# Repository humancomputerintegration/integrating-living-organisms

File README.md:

# Integrating Living Organisms to Implement Care-based Interactions

This repository contains design files to replicate the slime mold integrated smartwatch presented in the paper ["Integrating Living Organisms to Implement Care-based Interactions"](https://dl.acm.org/doi/abs/10.1145/3526113.3545629), which appeared at UIST2022. The smartwatch is a prototype exploring a living media interface that requires the user to care for the organism (slime mold, aka Physarum Polycephalum) that is integrated inside it in order for the functionality (it's heart rate sensor) to work. This device was designed by Jasmine Lu and Pedro Lopes at the University of Chicago's [Human Computer Integration Lab](https://lab.plopes.org).

[Paper](https://lab.plopes.org/published/2022-UIST-IntegratingLivingOrganisms.pdf) | [Video](https://youtu.be/Bex91KV56PQ) | [UIST'22 Talk](https://youtu.be/VkC54ZNO_HU?t=18566)

## Device Hardware
The slime mold integrated smart watch is a standard maker-friendly smartwatch with a display, RTC, and heart rate sensor. However, it's specifically engineered to rely on the slime mold to form a conductive wire. An overview of the whole system can be seen below.

### Device Components
Below is a list of all the components required for to make this device. For the enclosures, the current design does require access to a 3D printer and a laser cutter. The current design also requires the manufacturing of a PCB (and ordering of small electronic components). 

#### Materials
* Clear acrylic sheets (2mm and 1.5mm)
* Acrylic Glue
* PLA for 3D printing
* Watch Strap - [Amazon Link](https://www.amazon.com/gp/product/B085PXB8CV/)
* Neodynium Magnets (6mm x 2mm and 3mm x 2mm) - [Link 1](https://www.amazon.com/gp/product/B07KJ9H31P) [Link 2](https://www.amazon.com/ETHCOOL-Magnets-Warhammer-Miniatures-Projects/dp/B09MVYGX1X)
* Copper Tape

#### Electronic Components
* Seeeduino Xiao Microcontroller - [Link](https://www.seeedstudio.com/Seeeduino-XIAO-Arduino-Microcontroller-SAMD21-Cortex-M0+-p-4426.html)
* MAX3010X Heart Rate Sensor Breakout - [Link](https://www.amazon.com/dp/B08ZNFF7H2)
* Lithium Battery Charging Module - [Link](https://www.amazon.com/Lithium-Battery-Charging-Protection-Functions/dp/B07MDPLQ18)
* Latching Switch (for On/Off Button)
* Vibromotor/LRA - [Link](https://nfpshop.com/product/6mm-brushless-coin-vibration-motor-2-5mm-type-model-nfp-ws0625)
* OLED display - [Link](https://www.amazon.com/Dorhea-Display-3-3V-5V-Arduino-Raspberry/dp/B0837DLWVH/)
* SMD Reistors (0805): 10K (5), 9K (1), 1K (1), 470 (1), 2M (1)
* SMD Capacitors (0805): 100nF (2),
* SMD RTC - RV-3028-C7 - [Link](https://mou.sr/3UEpNhk)
* SMD RTC Coin Cell Battery - [Link](https://www.arrow.com/en/products/ml-621sdn/panasonic%3Fregion=nac&utm_source=findchips&utm_medium=aggregator&utm_currency=&utm_campaign=arrow_findchips_2021_Americas&utm_content=inv_listing&utm_term=backorder)
* SMD MOSFET - SSM3K15ACTC - [Link](https://mou.sr/3hI601T)
* SMD Dual OpAmp - SOP65P490X110-8N - [Link](https://www.digikey.com/en/products/detail/microchip-technology/MCP6542T-I-SN/458455)

### Device Enclosure
The 3D Models (as STL files) for the Device Case are included in this repo [here](./Device_Enclosure_STL). This includes both the main case and case for power/charging circuit (batteries, charging module, on/off button).
These models are designed to fit the designed PCB, OLED display, MAX3010 HR Sensor, Physarum Wire Enclosure, a copper tape capacitive touch Sensor, and a small vibromotor. Future designs will likely include a smaller form factor - if you're interested in redesigning this, please get in touch!

### Slime Mold Enclosure
The slime mold wire enclosure is made by lasercutting acrylic pieces and binding them together with acrylic glue. The vector files for these cuts were designed in Adobe Illustrator and can be found [here](./Slime_Mold_Enclosure_VectorCuts). There are also holes for 6x2mm Neodymium Magnets on the bottom layer and holes for 3x2mm magnets on the top layer and in the enclosure lid layer. An overview of these layers is shown in the figure below.

### PCB Design Files
Our PCB was designed with KiCAD. You can find all KiCAD project files [here](./PCB_Design_Files). For an overview of what the PCB looks like, you can refer to the figure below.

## Slime Mold and How to Care for them
The key to this device is growing a slime mold wire. For more information on how to grow and care for a slime mold - you can see the care instructions I've made [here](https://drive.google.com/file/d/1Qz3SxQu3I3aJ-D0hYsuum45GsUVl9gFx/view?usp=sharing). (Note these are somewhat specific to a provided kit at the UIST22 conference. If you'd like some slime mold and maybe a kit too, feel free to reach out!)

Other resources for growing and playing around with slime mold include the [Slime Mold Collective](https://slimoco.ning.com/) and [Physarum Computing Research](https://link.springer.com/book/10.1007/978-3-319-26662-6).

## Citation

When using or building upon this device/work in an academic publication, please consider citing as follows:

Jasmine Lu, Pedro Lopes. 2022. Integrating Living Organisms in Devices to Implement Care-based Interactions. In Proceedings of ACM Symposium on User Interface Software and Technology 2022 (UIST’2022). Association for Computing Machinery, New York, NY, USA. https://doi.org/10.1145/3526113.3545629

## Contact
For questions or if something is wrong with this repository, contact jasminelu@uchicago.edu

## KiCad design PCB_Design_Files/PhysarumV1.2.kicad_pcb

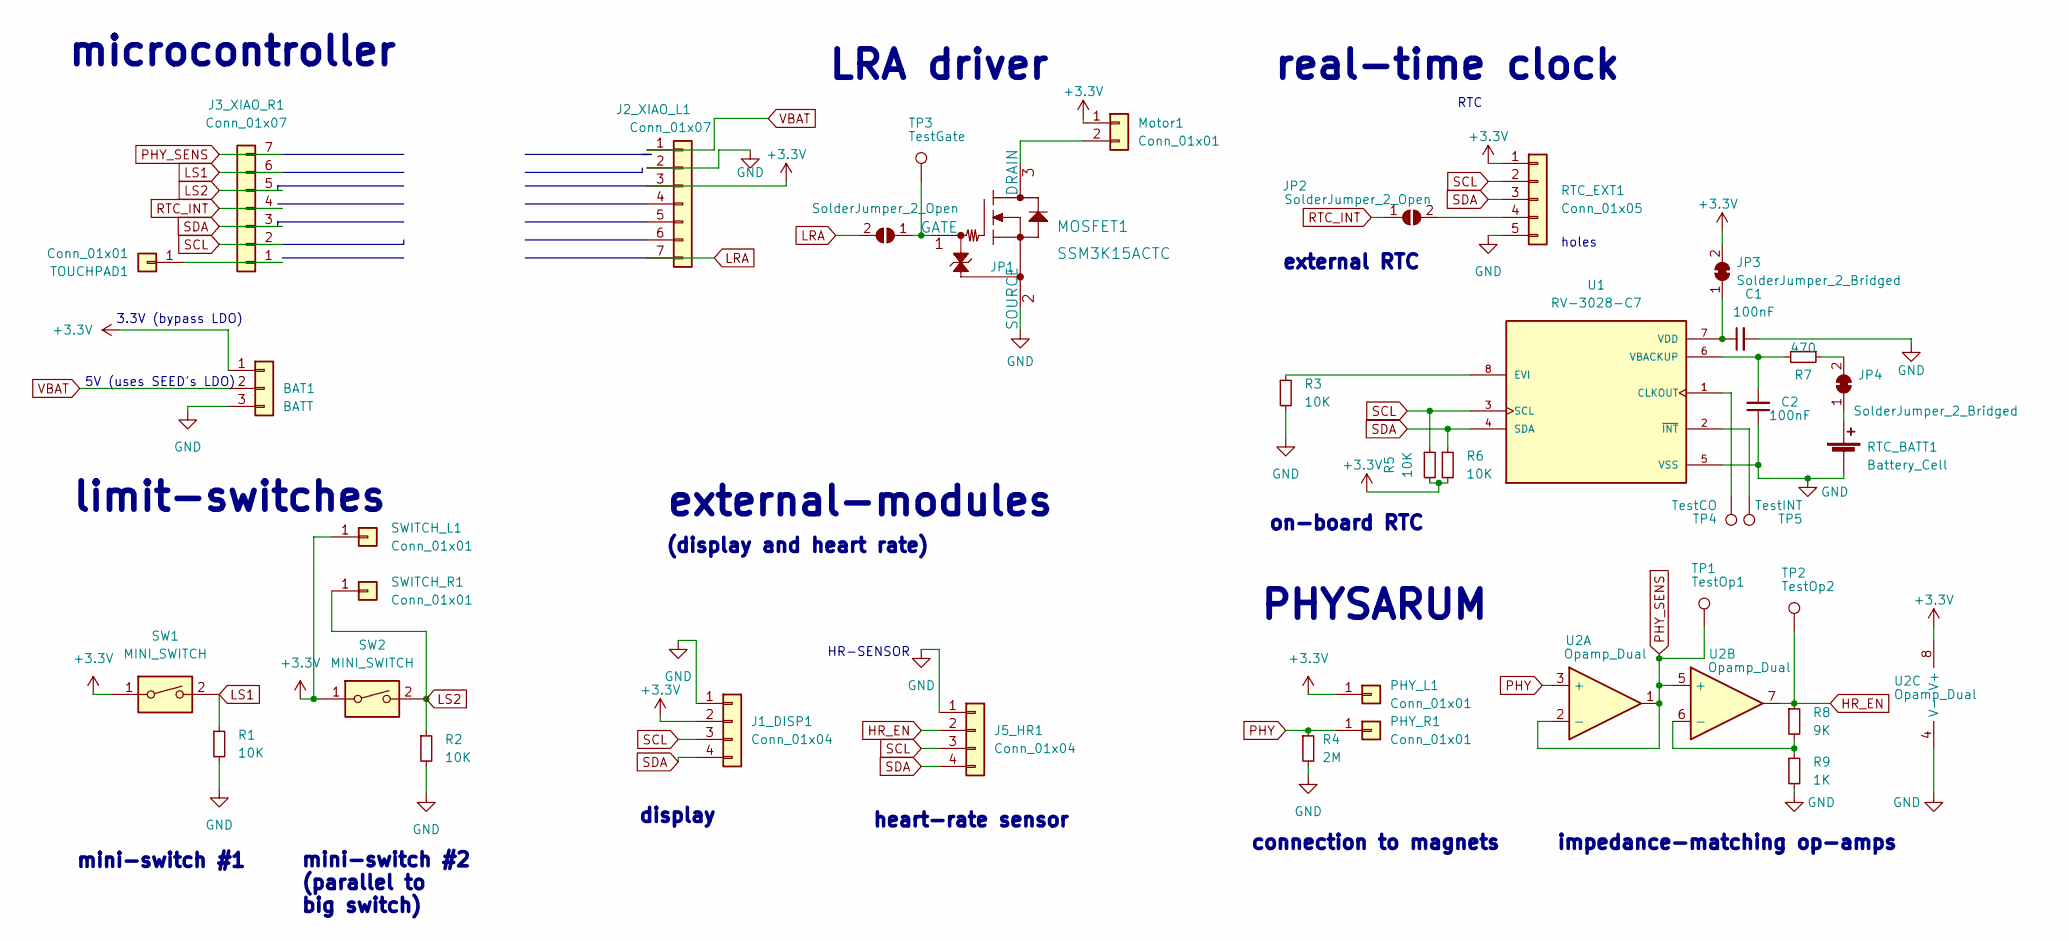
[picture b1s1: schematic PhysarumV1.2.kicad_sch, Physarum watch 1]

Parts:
BAT1: BATT; PinHeader_1x03_P2.54mm_Vertical
C1, C2: 100nF; C_0805_2012Metric_Pad1.18x1.45mm_HandSolder
J1_DISP1: Conn_01x04; PinHeader_1x04_P2.54mm_Vertical
J2_XIAO_L1, J3_XIAO_R1: Conn_01x07; RowPad_1x07_P2.54mm
J5_HR1: Conn_01x04; RowPad_1x04_P2.54mm
JP1, JP2: SolderJumper_2_Open; SolderJumper-2_P1.3mm_Open_Pad1.0x1.5mm
JP3, JP4: SolderJumper_2_Bridged; SolderJumper-2_P1.3mm_Bridged_RoundedPad1.0x1.5mm
MOSFET1: SSM3K15ACTC
Motor1: Conn_01x01; PinHeader_1x02_P2.54mm_Vertical
PHY_L1: Conn_01x01; PinHeader_1x01_P2.54mm_Vertical
PHY_R1: Conn_01x01; PinHeader_1x01_P2.54mm_Vertical
R1, R2, R3, R5, R6: 10K; R_0805_2012Metric_Pad1.20x1.40mm_HandSolder
R4: 2M; R_0805_2012Metric_Pad1.20x1.40mm_HandSolder
R7: 470; R_0805_2012Metric_Pad1.20x1.40mm_HandSolder
R8: 9K; R_0805_2012Metric_Pad1.20x1.40mm_HandSolder
R9: 1K; R_0805_2012Metric_Pad1.20x1.40mm_HandSolder
RTC_BATT1: Battery_Cell; P044-ND_SMD_Battery
RTC_EXT1: Conn_01x05; PinHeader_1x05_P2.54mm_Vertical
SW1, SW2: MINI_SWITCH; JJJHLGG200NOPMRTR
SWITCH_L1: Conn_01x01; RowPad_1x01_P2.54mm
SWITCH_R1: Conn_01x01; RowPad_1x01_P2.54mm
TOUCHPAD1: Conn_01x01; TestPoint_Loop_D2.50mm_Drill1.0mm
TP1: TestOp1; TestPoint_Pad_D1.0mm
TP2: TestOp2; TestPoint_Pad_D1.0mm
TP3: TestGate; TestPoint_Pad_D1.0mm
TP4: TestCO; TestPoint_Pad_D1.0mm
TP5: TestINT; TestPoint_Pad_D1.0mm
U1: RV-3028-C7; IC_RV-3028-C7; PARTREV 1.2/03.2021
U2: Opamp_Dual; SOP65P490X110-8N

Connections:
+3V3: BAT1.1, J1_DISP1.2, J2_XIAO_L1.3, JP3.2 (B), Motor1.1, PHY_L1.1, R5.2, R6.2, RTC_EXT1.1, SW1.1, SW2.1, SWITCH_L1.1, U2.8 (V+)
GND: BAT1.3, C1.2, C2.1, J1_DISP1.1, J2_XIAO_L1.2, J5_HR1.1, MOSFET1.2 (SOURCE), R1.2, R2.2, R3.2, R4.2, R9.2, RTC_BATT1.2 (-), RTC_EXT1.5, U1.5 (VSS), U2.4 (V-)
HR_EN: J5_HR1.2, R8.1, TP2.1, U2.7
LRA: J2_XIAO_L1.7, JP1.2 (B)
LS1: J3_XIAO_R1.6, R1.1, SW1.2
LS2: J3_XIAO_R1.5, R2.1, SW2.2, SWITCH_R1.1
unnamed: C1.1, JP3.1 (A), U1.7 (VDD)
unnamed: C2.2, R7.2, U1.6 (VBACKUP)
unnamed: J3_XIAO_R1.1, TOUCHPAD1.1
unnamed: JP1.1 (A), MOSFET1.1 (GATE), TP3.1
unnamed: JP2.2 (B), RTC_EXT1.4
unnamed: JP4.1 (A), RTC_BATT1.1 (+)
unnamed: JP4.2 (B), R7.1
unnamed: MOSFET1.3 (DRAIN), Motor1.2
unnamed: R3.1, U1.8 (EVI)
unnamed: R8.2, R9.1, U2.6 (-)
unnamed: TP4.1, U1.1 (CLKOUT)
unnamed: TP5.1, U1.2 (~INT)
PHY: PHY_R1.1, R4.1, U2.3 (+)
PHY_SENS: J3_XIAO_R1.7, TP1.1, U2.1, U2.2 (-), U2.5 (+)
RTC_INT: J3_XIAO_R1.4, JP2.1 (A)
SCL: J1_DISP1.3, J3_XIAO_R1.2, J5_HR1.3, R5.1, RTC_EXT1.2, U1.3 (SCL)
SDA: J1_DISP1.4, J3_XIAO_R1.3, J5_HR1.4, R6.1, RTC_EXT1.3, U1.4 (SDA)
VBAT: BAT1.2, J2_XIAO_L1.1

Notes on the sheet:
(display and heart rate)
RTC
PHYSARUM
microcontroller
external-modules
LRA driver
5V (uses SEED's LDO)
external RTC
connection to magnets
3.3V (bypass LDO)
impedance-matching op-amps
limit-switches
on-board RTC
holes
mini-switch #1
display
heart-rate sensor
real-time clock
mini-switch #2 (parallel to big switch)
HR-SENSOR

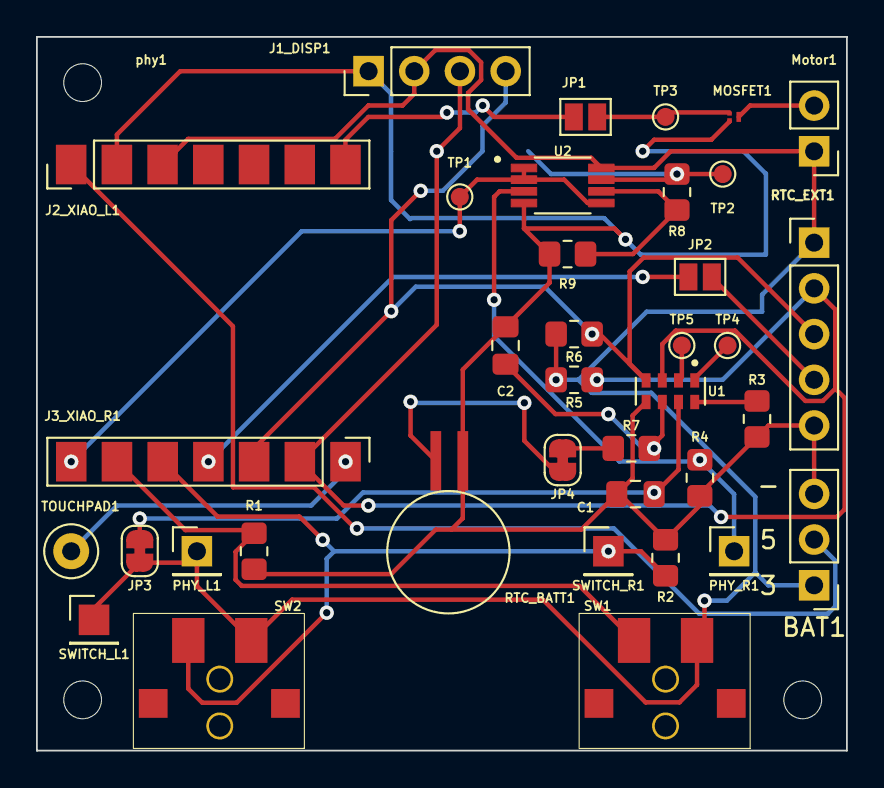
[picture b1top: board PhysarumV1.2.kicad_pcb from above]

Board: 2 copper layers, 45.0 x 39.6 mm, 38 parts (1 on the bottom side), 24 nets.

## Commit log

2022-11-14 all design and image files added

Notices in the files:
parts and their libraries:
Copyright 2021 Accelerated Designs. All rights reserved.
